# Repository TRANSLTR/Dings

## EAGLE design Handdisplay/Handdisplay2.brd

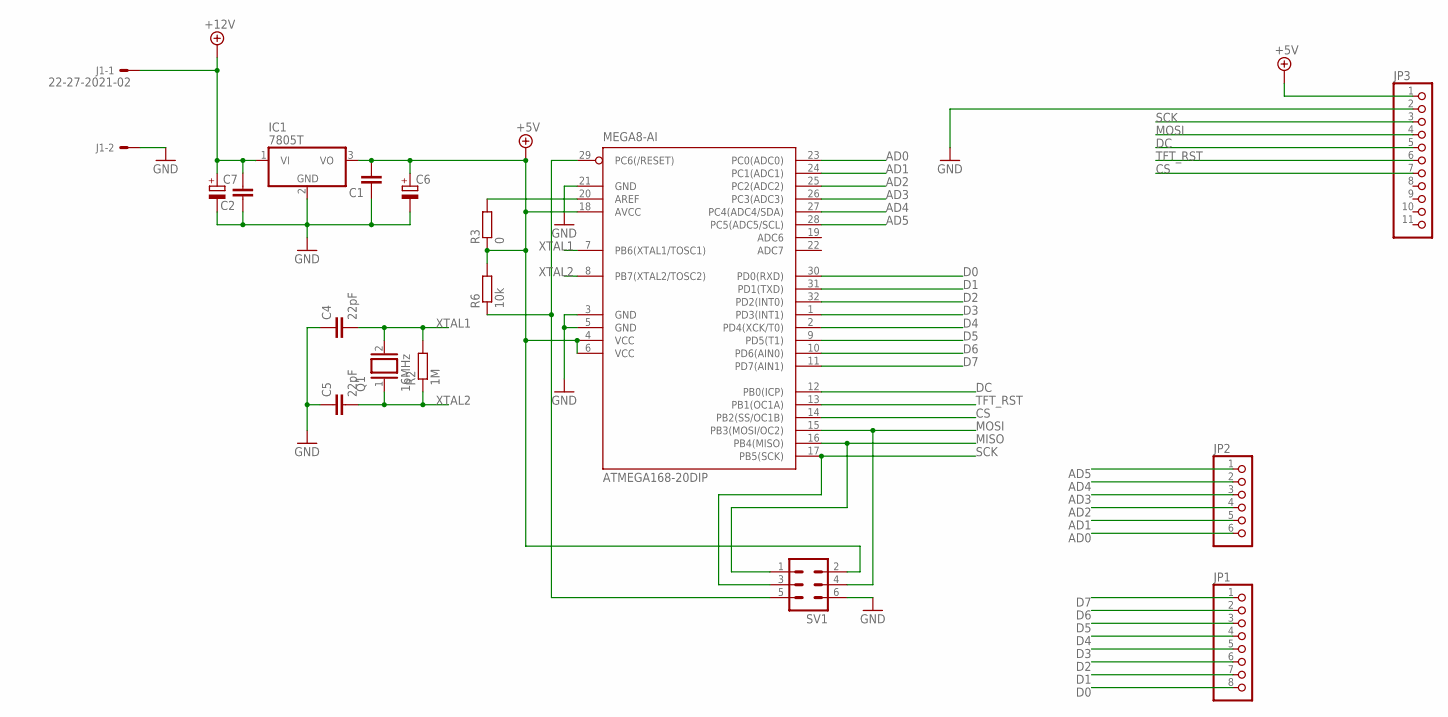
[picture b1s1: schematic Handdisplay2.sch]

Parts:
ATMEGA168-20DIP: MEGA8-AI; TQFP32-08
C1, C2: C-EUC0805; C0805
C4, C5: 22pF; C0805
C6, C7: CPOL-EUUD-5X5,8; UD-5X5,8_NICHICON
IC1: 7805T; TO220H
J1: 22-27-2021-02; 6410-02
JP1: PINHD-1X8; 1X08
JP2: PINHD-1X6; 1X06
JP3: PINHD-1X11; 1X11
Q1: 16MHz; QS
R2: 1M; R0805
R3: 0; R0805
R6: 10k; R0805
SV1: ML6

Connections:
+5V: ATMEGA168-20DIP.4 (VCC), ATMEGA168-20DIP.6 (VCC), ATMEGA168-20DIP.18 (AVCC), C1.2, C6.+, IC1.3 (VO), JP3.1, R3.1, R6.2, SV1.2
+12V: C2.2, C7.+, IC1.1 (VI), J1.1
AD0: ATMEGA168-20DIP.23 (PC0(ADC0)), JP2.6
AD1: ATMEGA168-20DIP.24 (PC1(ADC1)), JP2.5
AD2: ATMEGA168-20DIP.25 (PC2(ADC2)), JP2.4
AD3: ATMEGA168-20DIP.26 (PC3(ADC3)), JP2.3
AD4: ATMEGA168-20DIP.27 (PC4(ADC4/SDA)), JP2.2
AD5: ATMEGA168-20DIP.28 (PC5(ADC5/SCL)), JP2.1
CS: ATMEGA168-20DIP.14 (PB2(SS/OC1B)), JP3.7
D0: ATMEGA168-20DIP.30 (PD0(RXD)), JP1.8
D1: ATMEGA168-20DIP.31 (PD1(TXD)), JP1.7
D2: ATMEGA168-20DIP.32 (PD2(INT0)), JP1.6
D3: ATMEGA168-20DIP.1 (PD3(INT1)), JP1.5
D4: ATMEGA168-20DIP.2 (PD4(XCK/T0)), JP1.4
D5: ATMEGA168-20DIP.9 (PD5(T1)), JP1.3
D6: ATMEGA168-20DIP.10 (PD6(AIN0)), JP1.2
D7: ATMEGA168-20DIP.11 (PD7(AIN1)), JP1.1
DC: ATMEGA168-20DIP.12 (PB0(ICP)), JP3.5
GND: ATMEGA168-20DIP.3 (GND), ATMEGA168-20DIP.5 (GND), ATMEGA168-20DIP.21 (GND), C1.1, C2.1, C4.1, C5.1, C6.-, C7.-, IC1.2 (GND), J1.2, JP3.2, SV1.6
MISO: ATMEGA168-20DIP.16 (PB4(MISO)), SV1.1
MOSI: ATMEGA168-20DIP.15 (PB3(MOSI/OC2)), JP3.4, SV1.4
unnamed: ATMEGA168-20DIP.20 (AREF), R3.2
unnamed: ATMEGA168-20DIP.29 (PC6(/RESET)), R6.1, SV1.5
SCK: ATMEGA168-20DIP.17 (PB5(SCK)), JP3.3, SV1.3
TFT_RST: ATMEGA168-20DIP.13 (PB1(OC1A)), JP3.6
XTAL1: ATMEGA168-20DIP.7 (PB6(XTAL1/TOSC1)), C4.2, Q1.2, R2.2
XTAL2: ATMEGA168-20DIP.8 (PB7(XTAL2/TOSC2)), C5.2, Q1.1, R2.1

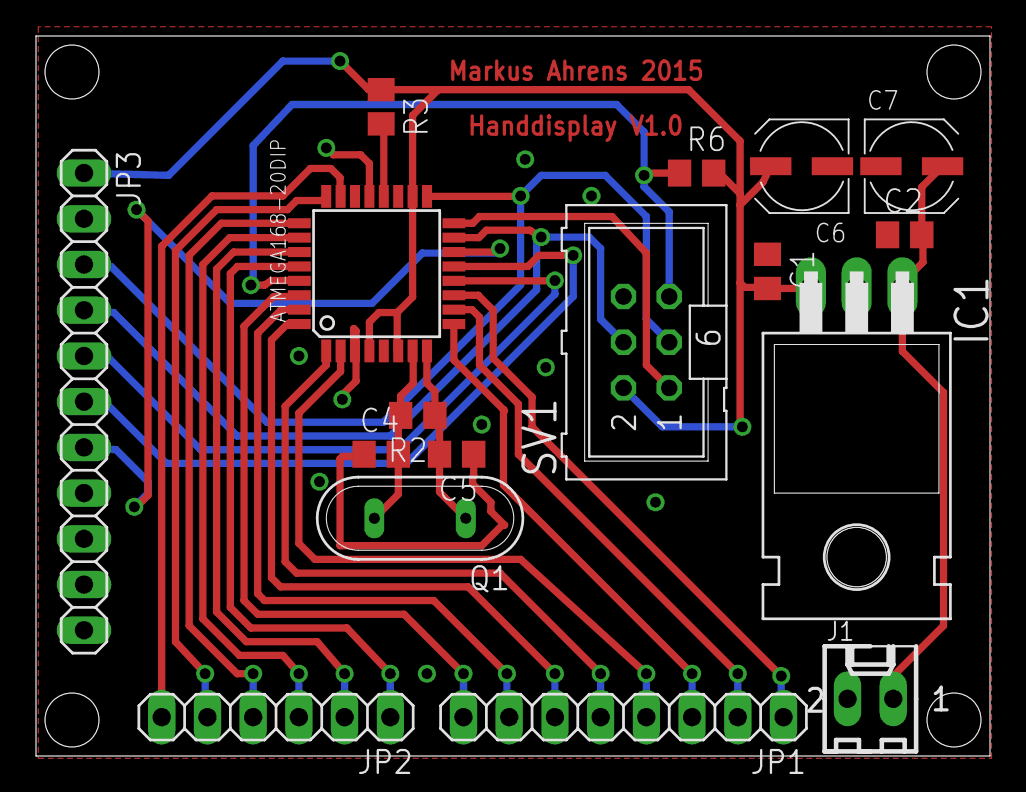
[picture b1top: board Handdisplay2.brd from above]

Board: 2 copper layers, 53.0 x 40.0 mm, 17 parts (0 on the bottom side), 27 nets.

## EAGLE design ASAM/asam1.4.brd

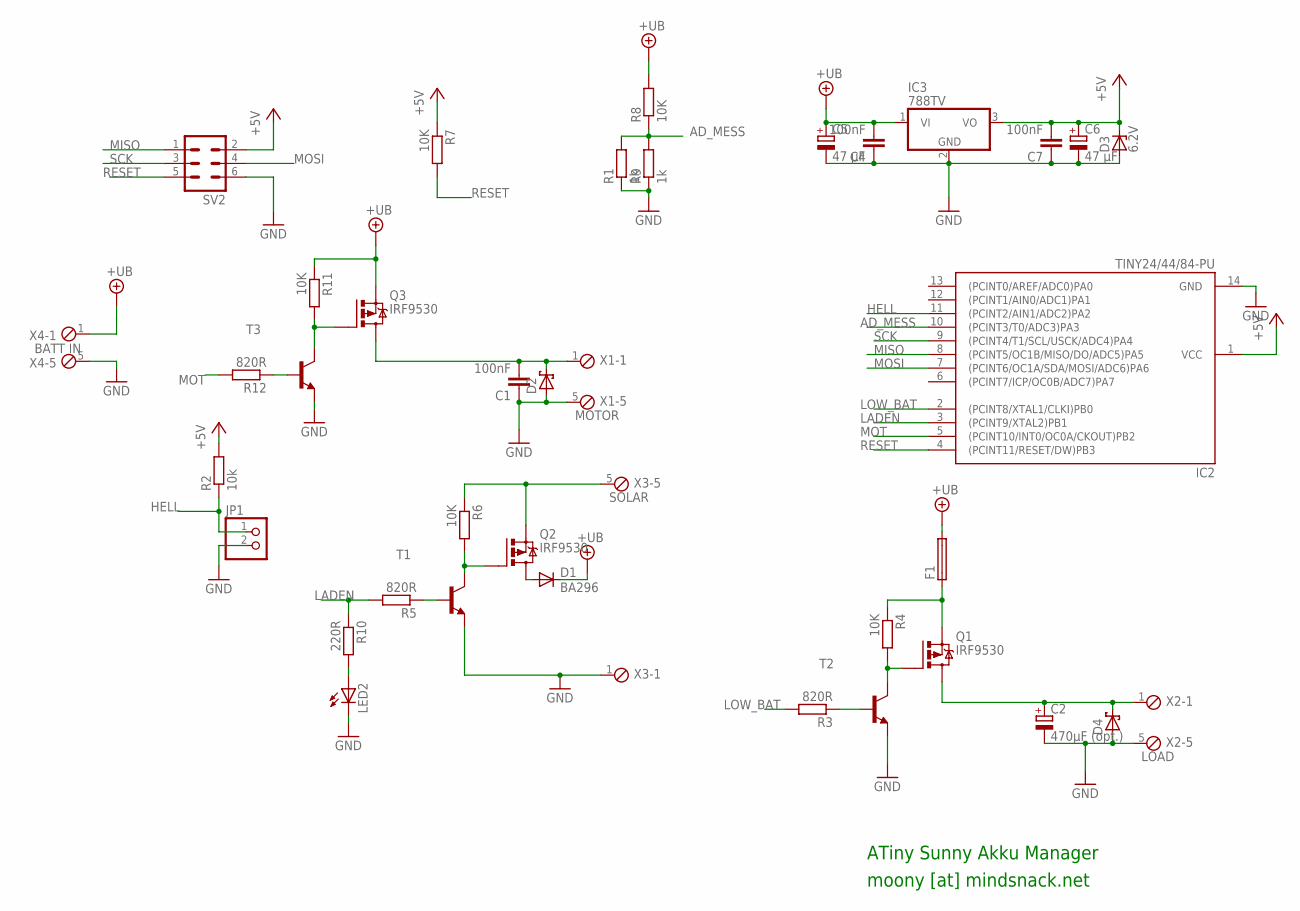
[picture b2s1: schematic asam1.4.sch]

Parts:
C1, C4, C7: 100nF; C075-032X103
C2: 470µF (opt.); E5-10,5
C5, C6: 47 µF; E5-10,5
D1: BA296; P2-15
D2, D4: SCHOTTKY-DIODEDO35-7; DO35-7
D3: 6.2V; C1702-15
F1: SH22,5
IC2: TINY24/44/84-PU; DIL14
IC3: 788TV; TO220V
JP1: PINHD-1X2; 1X02
LED2: LED3MM
Q1, Q2, Q3: IRF9530; TO220BV
R1, R9: 1k; 0207/10
R2: 10k; 0207/10
R3, R5, R12: 820R; 0207/10
R4, R6, R7, R11: 10K; 0207/12
R8: 10K; 0207/10
R10: 220R; 0207/10
SV2: MA03-2
T1, T2, T3: BC546-NPN-TO92-CBE; TO92-CBE
X1: MOTOR; 5POL254
X2: LOAD; 5POL254
X3: SOLAR; 5POL254
X4: BATT IN; 5POL254

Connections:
+5V: C6.+, C7.2, D3.C, IC2.1 (VCC), IC3.3 (VO), R2.2, R7.1, SV2.2
+UB: C4.2, C5.+, D1.C, F1.2, IC3.1 (VI), Q3.S, R8.2, R11.1, X4.1
AD_MESS: IC2.10 ((PCINT3/T0/ADC3)PA3), R1.2, R8.1, R9.2
GND: C1.1, C2.-, C4.1, C5.-, C6.-, C7.1, D2.A, D3.A, D4.A, IC2.14 (GND), IC3.2 (GND), JP1.2, LED2.K (C), R1.1, R9.1, SV2.6, T1.E, T2.E, T3.E, X1.5, X2.5, X3.1, X4.5
HELL: IC2.11 ((PCINT2/AIN1/ADC2)PA2), JP1.1, R2.1
LADEN: IC2.3 ((PCINT9/XTAL2)PB1), R5.2, R10.1
LOW_BAT: IC2.2 ((PCINT8/XTAL1/CLKI)PB0), R3.2
MISO: IC2.8 ((PCINT5/OC1B/MISO/DO/ADC5)PA5), SV2.1
MOSI: IC2.7 ((PCINT6/OC1A/SDA/MOSI/ADC6)PA6), SV2.4
MOT: IC2.5 ((PCINT10/INT0/OC0A/CKOUT)PB2), R12.2
unnamed: C1.2, D2.C, Q3.D, X1.1
unnamed: R3.1, T2.B
unnamed: Q1.G, R4.2, T2.C
unnamed: Q2.S, R6.1, X3.5
unnamed: Q2.G, R6.2, T1.C
unnamed: Q3.G, R11.2, T3.C
unnamed: R5.1, T1.B
unnamed: LED2.A, R10.2
unnamed: D1.A, Q2.D
unnamed: R12.1, T3.B
unnamed: F1.1, Q1.S, R4.1
unnamed: C2.+, D4.C, Q1.D, X2.1
RESET: IC2.4 ((PCINT11/RESET/DW)PB3), R7.2, SV2.5
SCK: IC2.9 ((PCINT4/T1/SCL/USCK/ADC4)PA4), SV2.3

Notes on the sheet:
ATiny Sunny Akku Manager
moony [at] mindsnack.net

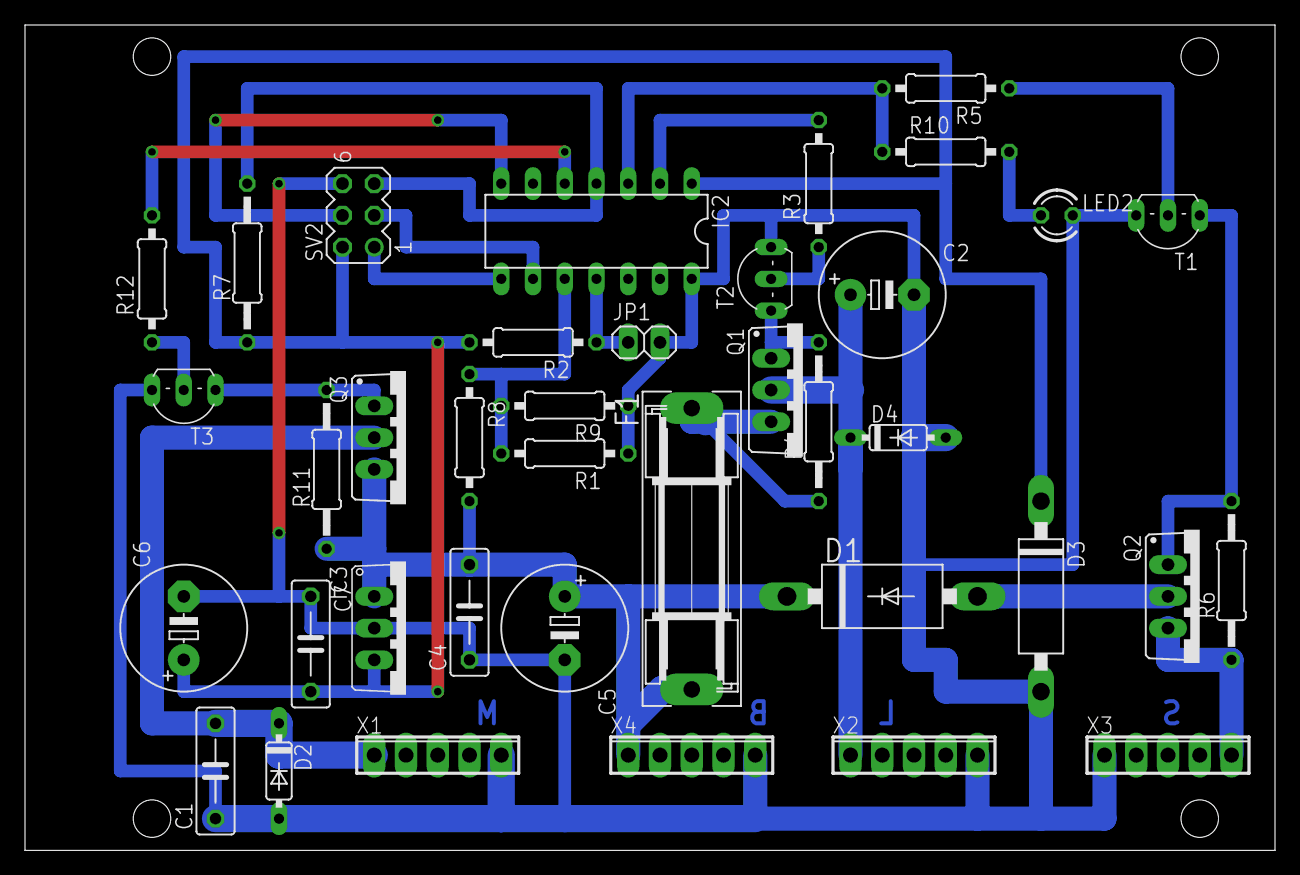
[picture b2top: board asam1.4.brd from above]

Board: 2 copper layers, 100.0 x 66.0 mm, 38 parts (0 on the bottom side), 24 nets.

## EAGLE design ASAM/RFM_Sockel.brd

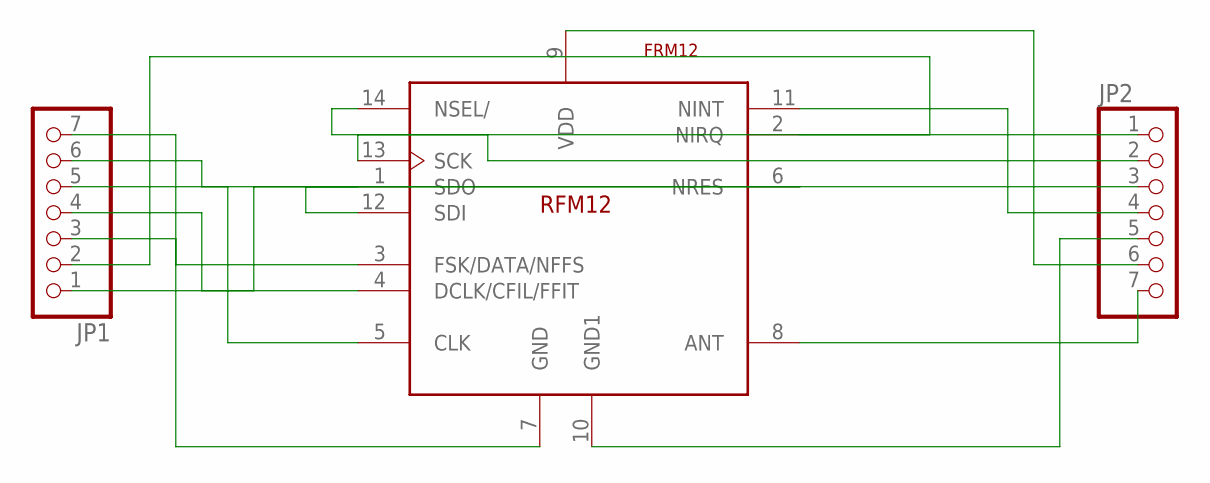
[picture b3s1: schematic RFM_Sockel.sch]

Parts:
JP1, JP2: PINHD-1X7; 1X07
U$1: FRM12; RFM12

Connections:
unnamed: JP1.1, U$1.1 (SDO)
unnamed: JP1.2, U$1.2 (NIRQ)
unnamed: JP1.3, U$1.3 (FSK/DATA/NFFS)
unnamed: JP1.4, U$1.4 (DCLK/CFIL/FFIT)
unnamed: JP1.5, U$1.5 (CLK)
unnamed: JP1.6, U$1.6 (NRES)
unnamed: JP1.7, U$1.7 (GND)
unnamed: JP2.7, U$1.8 (ANT)
unnamed: JP2.5, U$1.10 (GND1)
unnamed: JP2.4, U$1.11 (NINT)
unnamed: JP2.3, U$1.12 (SDI)
unnamed: JP2.2, U$1.13 (SCK)
unnamed: JP2.1, U$1.14 (NSEL/)
VDD: JP2.6, U$1.9 (VDD)

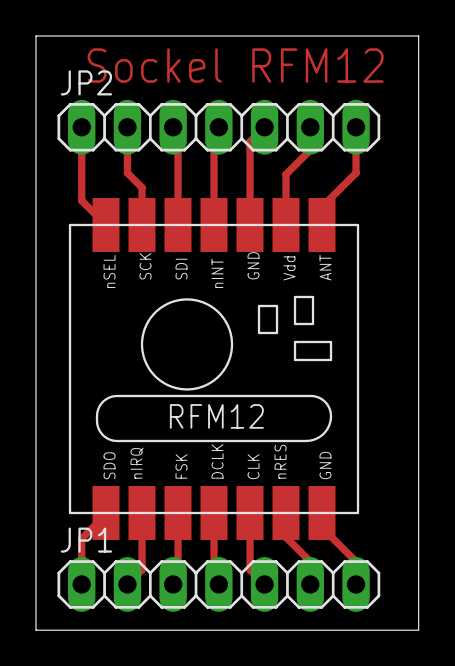
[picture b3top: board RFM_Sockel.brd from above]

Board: 2 copper layers, 21.3 x 33.0 mm, 3 parts (0 on the bottom side), 14 nets.

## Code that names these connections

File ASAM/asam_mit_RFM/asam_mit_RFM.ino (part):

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#define SEND_DELAY 1000   // Sample Time
#define DWN_SAMPLE 100    // in jedem wievielten Takt soll gesendet werden?
#define DUNKEL 1980       // Helligkeitswert, ab dem das Licht angeschaltet werden soll
#define HELL 1500
#define STUNDEN 5         // Leuchtdauer in Stunden
#define LEUCHTDAUER SEND_DELAY/10*36*STUNDEN  // Zeit, die das Licht anbleiben soll

#define LADEN 10          // Batterie laden
#define MOTOR 9           // Motor ein
#define N_LOW_BAT 0         // Verbraucher aus
#define LEDpin 3          // Status-LED-Pin 
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/*
                     +-\/-+
               VCC  1|    |14  GND
          (D0) PB0  2|    |13  AREF (D10)
          (D1) PB1  3|    |12  PA1 (D9)
             RESET  4|    |11  PA2 (D8)
INT0  PWM (D2) PB2  5|    |10  PA3 (D7)
      PWM (D3) PA7  6|    |9   PA4 (D6)
      PWM (D4) PA6  7|    |8   PA5 (D5) PWM
                     +----+
*/

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               
               
     pinMode(LEDpin, OUTPUT);
     pinMode(LADEN, OUTPUT);
     pinMode(MOTOR, OUTPUT);
     pinMode(N_LOW_BAT, OUTPUT);
     
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
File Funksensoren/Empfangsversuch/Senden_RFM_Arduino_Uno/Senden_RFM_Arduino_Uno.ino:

#include <JeeLib.h> // https://github.com/jcw/jeelib
#include "pins_arduino.h"
#include <avr/sleep.h>
#include <Ports.h>

/*
// ATmega168, ATmega328, etc.
#define RFM_IRQ     2
#define SS_DDR      DDRB
#define SS_PORT     PORTB
#define SS_BIT      2     // for PORTB: 2 = d.10, 1 = d.9, 0 = d.8

#define SPI_SS      10    // PB2, pin 16
#define SPI_MOSI    11    // PB3, pin 17
#define SPI_MISO    12    // PB4, pin 18
#define SPI_SCK     13    // PB5, pin 19
*/

#define NODEID 01       // RF12 node ID in the range 1-30
#define NETWORKID 210       // RF12 Network group
#define myUID 55          // device id

#define FREQ RF12_433MHZ  // Frequency of RFM12B module

//#define USE_ACK           // Enable ACKs, comment out to disable
#define RETRY_PERIOD 3    // How soon to retry (in seconds) if ACK didn't come in
#define RETRY_LIMIT 5     // Maximum number of times to retry
#define ACK_TIME 22       // Number of milliseconds to wait for an ack
#define SEND_DELAY 1000   // Sample Time
#define DWN_SAMPLE 100       // in jedem wievielten Takt soll gesendet werden?
#define DATA_RATE_49200  0xC606           // Approx  49200 bps
#define DATA_RATE_38400  0xC608           //  Approx  38400 bps
#define DATA_RATE        DATA_RATE_38400  // use one of the data rates defined above

#define V_BAT_ADC 3       // ADC Number for battery voltage measurment
#define V_LIGHT_ADC 2     // ADC Number for brightness measurment

#define magicNumber 83    // magic number (GSD-Net identifier) => SubNodeID 1 Byte
ISR(WDT_vect) {}


typedef struct {
   byte magic;   // magic number
   byte uID;     // deviceID   
   int msg_counter;  
   byte m_powerSupply;    // 202
   int powerSupply;      // Supply voltage   
 } Payload;

 Payload tinytx;

// Wait a few milliseconds for proper ACK
 #ifdef USE_ACK
  static byte waitForAck() {
   MilliTimer ackTimer;
   while (!ackTimer.poll(ACK_TIME)) {
     if (rf12_recvDone() && rf12_crc == 0 &&
        rf12_hdr == (RF12_HDR_DST | RF12_HDR_CTL | NODEID)) {
          if ((rf12_len > 0 && rf12_data[0] == myUID) || (rf12_len == 0)) {
            return 1;
          }
        }
        //set_sleep_mode(SLEEP_MODE_IDLE);
        //sleep_mode();
     }
   return 0;
  }
 #endif
 
 //--------------------------------------------------------------------------------------------------
// Send payload data via RF
//-------------------------------------------------------------------------------------------------
 static byte rfwrite(){
  #ifdef USE_ACK
   for (byte i = 0; i <= RETRY_LIMIT; ++i) {  // tx and wait for ack up to RETRY_LIMIT times
     rf12_sleep(-1);              // Wake up RF module
      while (!rf12_canSend())
      rf12_recvDone();
      rf12_sendStart(RF12_HDR_ACK,&tinytx, sizeof(tinytx)); 
      rf12_sendWait(2);           // Wait for RF to finish sending while in standby mode
      byte acked = waitForAck();  // Wait for ACK
      rf12_sleep(0);              // Put RF module to sleep
      if (acked) { return 1; }      // Return if ACK received
  
   Sleepy::loseSomeTime(RETRY_PERIOD * 1000);     // If no ack received wait and try again
   }
   return 0;
  #else
     rf12_sleep(-1);              // Wake up RF module
     while (!rf12_canSend())
     rf12_recvDone();
     rf12_sendStart(0, &tinytx, sizeof(tinytx)); 
     rf12_sendWait(2);           // Wait for RF to finish sending while in standby mode
     rf12_sleep(0);              // Put RF module to sleep
     return 1;
  #endif
 }
 
 void setup() {
    tinytx.magic             = magicNumber;
     tinytx.msg_counter       = 1;
     tinytx.uID               = myUID;  
      rf12_initialize(NODEID, FREQ, NETWORKID); // Initialize RFM12 with settings defined above
     rf12_control(0xC040);      // Adjust low battery voltage to 2.2V
  rf12_sleep(0);              // Put the RFM12 to sleep
  
}

void loop() {
  
  tinytx.powerSupply =  1;
  
   tinytx.msg_counter++;
    rfwrite();
    
    Sleepy::loseSomeTime(SEND_DELAY); //JeeLabs power save function: enter low power mode for 60 seconds (valid range 16-65000 ms)

}

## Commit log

2015-12-25 Initial Commit ASAM
2016-02-03 ASAM mit RFM lauffaehig hinzugefuegt
2016-02-04 Brenndauerberechnung korrigiert
